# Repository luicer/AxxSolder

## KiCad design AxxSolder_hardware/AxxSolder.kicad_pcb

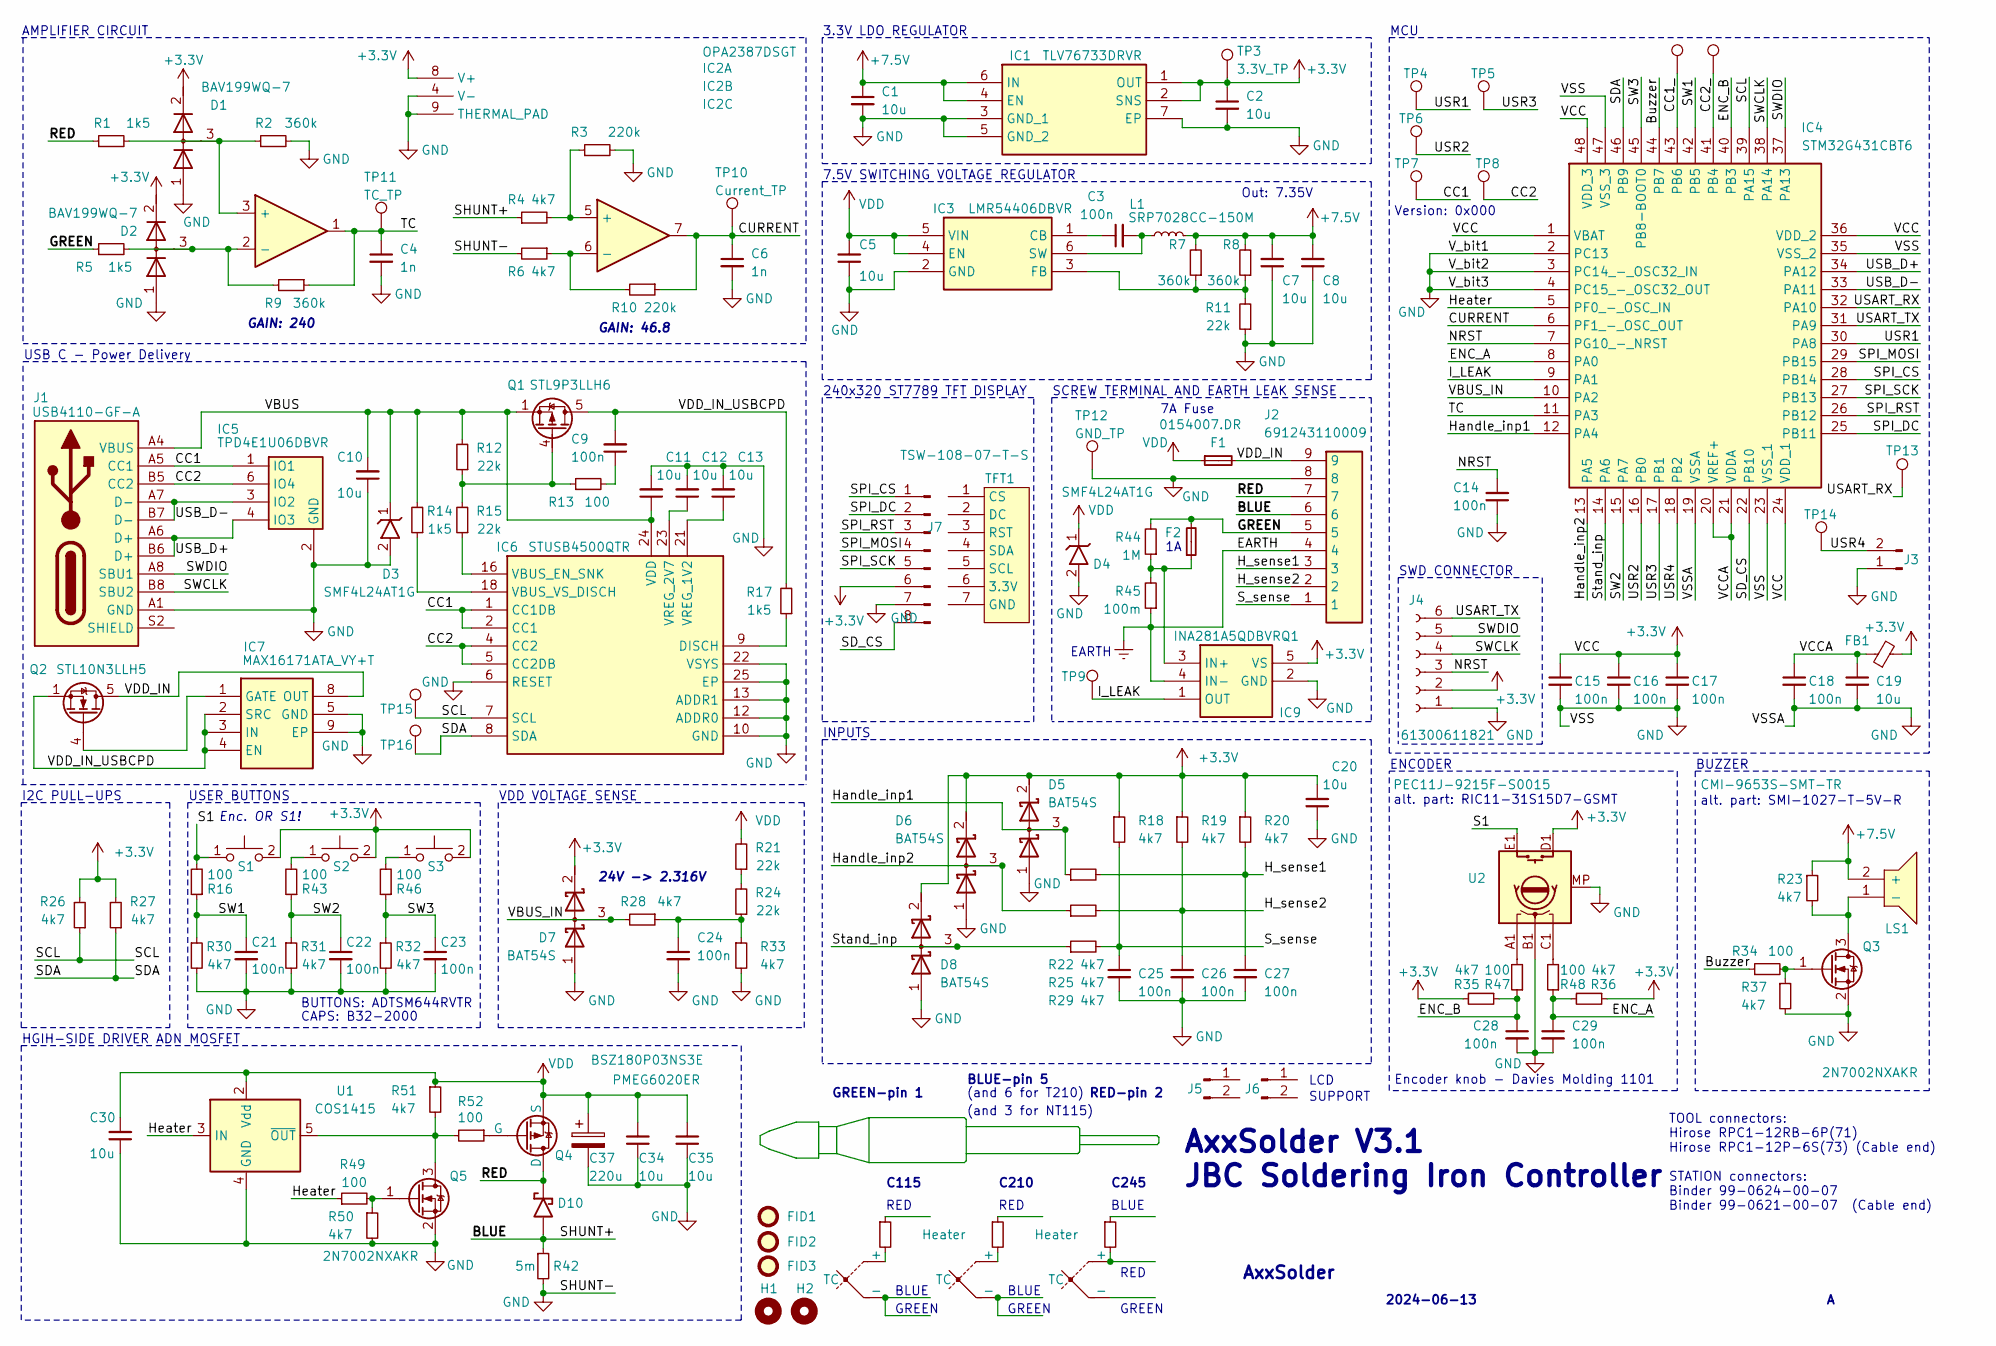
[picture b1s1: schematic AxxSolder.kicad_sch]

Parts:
C1, C2, C5, C7, C8, C10, C11, C12, C13, C19, C20, C30, C34, C35: 10u; C_0603_1608Metric; Manufacturer_Part_Number GRM188R6YA106MA73J; Mouser Part Number 81-GRM188R6YA106MA3J
C3, C9, C14, C15, C16, C17, C18, C21, C22, C23, C24, C25, C26, C27, C28, C29: 100n; C_0603_1608Metric; Manufacturer_Part_Number C0603C104J5RACTU; Mouser Part Number 80-C0603C104J5R
C4, C6: 1n; C_0603_1608Metric; Manufacturer_Part_Number C0603C102K3GAC; Mouser Part Number 80-C0603C102K3G
C37: 220u; CAPAE830X1050N; Mouser Part Number 80-EEV227M035A9MAA
D1, D2: BAV199WQ-7; SOT65P210X110-3N; Mouser Part Number 621-BAV199WQ-7
D3, D4: SMF4L24AT1G; SODFL3619X98N; Mouser Part Number 576-SMF4L24AT1G
D5, D6, D7, D8: BAT54S; SOT95P230X110-3N; Manufacturer_Part_Number BAT54S,215; Mouser Part Number 771-BAT54S-T/R
D10: PMEG6020ER; PMEG6020ER115; Mouser Part Number 771-PMEG6020ER-115
F1: 0154007.DR; 0154100DR; Mouser Part Number 576-0154007.DR
F2: SF-2410FP100W-2; SF2410FP100W2; Mouser Part Number 652-SF-2410FP100W-2
FB1: BLM18HE601SN1D; R_0603_1608Metric; Mouser Part Number 81-BLM18HE601SN1D
FID1, FID2, FID3: Fiducial; Fiducial_0.75mm_Mask1.5mm
H1, H2: MountingHole; MountingHole_2.5mm
IC1: TLV76733DRVR; SON65P200X200X80-7N; Mouser Part Number 595-TLV76733DRVR
IC2: OPA2387DSGT; VSSOP-8_3x3mm_P0.65mm; Mouser Part Number 595-OPA2387DSGT
IC3: LMR54406DBVR; SOT95P280X145-6N; Mouser Part Number 595-LMR54406DBVR
IC4: STM32G431CBT6; QFP50P900X900X160-48N; Mouser Part Number 511-STM32G431CBT6
IC5: TPD4E1U06DBVR; SOT95P280X145-6N; Mouser Part Number 595-TPD4E1U06DBVR
IC6: STUSB4500QTR; QFN50P400X400X100-25N-D; Mouser Part Number 511-STUSB4500QTR
IC7: MAX16171ATA_VY+T; SON50P300X200X80-9N; Mouser Part Number 700-MAX16171ATA/VY+T
IC9: INA281A5QDBVRQ1; SOT95P280X145-5N; Mouser Part Number 595-INA281A5QDBVRQ1
J1: USB4110-GF-A; USB4110GFA; Mouser Part Number 640-USB4110-GF-A
J2: 691243110009; Mouser Part Number 710-691243110009
J3: TSW-102-07-T-S; PinHeader_1x02_P2.54mm_Vertical; Mouser Part Number 200-TSW10207TS
J4: 61300611821; RHDR6W97P0X254_1X6_1574X250X865P; Mouser Part Number 710-61300611821
J5, J6: TSW-102-07-T-S; TSW-102-XX-YY-S; Mouser Part Number 200-TSW10207TS
J7: TSW-108-07-T-S; TSW-108-XX-YY-S; Mouser Part Number 200-TSW10807TS
L1: SRP7028CC-150M; INDPM7366X300N; Mouser Part Number 652-SRP7028CC-150M
LS1: CMI-9653S-SMT-TR; CMI9653SSMTTR; Mouser Part Number 490-CMI-9653S-SMT-TR
Q1: STL9P3LLH6; Mouser Part Number 511-STL9P3LLH6
Q2: STL10N3LLH5; Mouser Part Number 511-STL10N3LLH5
Q3, Q5: 2N7002NXAKR; SOT95P230X110-3N; Manufacturer_Part_Number 2N7002NXAKR; Mouser Part Number 771-2N7002NXAKR
Q4: BSZ180P03NS3E; TDSON-8-1
R1, R5, R14, R17: 1k5; R_0603_1608Metric; Manufacturer_Part_Number ERJ-H3ED1501V; Mouser Part Number 667-ERJ-H3ED1501V
R2, R7, R8, R9: 360k; R_0603_1608Metric; Manufacturer_Part_Number ERJ-3RED3603V; Mouser Part Number 667-ERJ-3RED3603V
R3, R10: 220k; R_0603_1608Metric; Manufacturer_Part_Number ERJ-3RED2203V; Mouser Part Number 667-ERJ-3RED2203V
R4, R6, R18, R19, R20, R22, R23, R25, R26, R27, R28, R29, R30, R31, R32, R33, R35, R36, R37, R50: 4k7; R_0603_1608Metric; Manufacturer_Part_Number ERJ-3RBD4701V; Mouser Part Number 667-ERJ-3RBD4701V
R11, R12, R15, R21, R24: 22k; R_0603_1608Metric; Manufacturer_Part_Number ERJ-UP3J223V; Mouser Part Number 667-ERJ-UP3J223V
R13, R16, R34, R43, R46, R47, R48, R49: 100; R_0603_1608Metric; Manufacturer_Part_Number ERJ-P03F1000V; Mouser Part Number 667-ERJ-P03F1000V
R39, R40: Heater
R41: Heater 2 OHM
R42: 5m; RESC6432X89N; Mouser Part Number 71-WSLP25125L000FEA
R44: 1M; R_0805_2012Metric; Manufacturer_Part_Number ERJ-6GEYJ105V; Mouser Part Number 667-ERJ-6GEYJ105V
R45: 100m; R_0805_2012Metric; Manufacturer_Part_Number ERJ-6DSFR10V; Mouser Part Number 667-ERJ-6DSFR10V
R51: 4k7; R_1210_3225Metric_Pad1.30x2.65mm_HandSolder; Manufacturer_Part_Number ERJ-3RBD4701V; Mouser Part Number 667-ERJ-3RBD4701V
R52: 100; R_0603_1608Metric; Manufacturer_Part_Number ERJ-3RBD4701V; Mouser Part Number 667-ERJ-3RBD4701V
S1, S2, S3: ADTSM644RVTR; Mouser Part Number 642-ADTSM644RVTR
TC1, TC2, TC3: TC
TFT1: Adafruit_240x320_TFT; Manufacturer_Part_Number 4311; Mouser Part Number 485-4311
TP1, TP2, TP4, TP5, TP6, TP7, TP8, TP14, TP15, TP16: DIAG_TP; TestPoint_Pad_D1.0mm
TP3: 3.3V_TP; TestPoint_Pad_D1.0mm
TP9, TP10: Current_TP; TestPoint_Pad_D1.0mm
TP11: TC_TP; TestPoint_Pad_D1.0mm
TP12: GND_TP; TestPoint_Pad_D1.0mm
TP13: DIAG_TP; TSW-101-XX-YY-S
U1: COS1415; SOT-23-5
U2: PEC11J-9215F-S0015; PEC11J9215FS0015; Mouser Part Number 652-PEC11J9215FS0015

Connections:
+3.3V: C2.1, C15.1, C16.1, C17.1, C20.2, D1.2, D2.2, D5.2 (K), D6.2 (K), D7.2 (K), D8.2 (K), FB1.2, IC1.1 (OUT), IC1.2 (SNS), IC2.8 (V+), IC4.1 (VBAT), IC4.24 (VDD_1), IC4.36 (VDD_2), IC4.48 (VDD_3), IC9.5 (VS), J4.2, J7.6, R18.1, R19.1, R20.1, R26.2, R27.2, R35.2, R36.1, S1.2, S2.2, S3.2, TP3.1, U2.D1
+7.5V: C1.1, C7.2, C8.2, IC1.4 (EN), IC1.6 (IN), L1.2, LS1.2 (+), R7.2, R8.2, R23.1
/BLUE: D10.2, J2.6, R4.1, R42.1
/Buzzer: IC4.44 (PB7), R34.1
/CC1: IC5.1 (IO1), IC6.1 (CC1DB), IC6.2 (CC1), J1.A5 (CC1), TP7.1
/CC1_: IC4.43 (PB6), TP1.1
/CC2: IC5.6 (IO4), IC6.4 (CC2), IC6.5 (CC2DB), J1.B5 (CC2), TP8.1
/CC2_: IC4.41 (PB4), TP2.1
/CURRENT: C6.1, IC2.7, IC4.6 (PF1_-_OSC_OUT), R10.1, TP10.1
/ENC_A: C29.1, IC4.8 (PA0), R36.2, R48.1
/ENC_B: C28.1, IC4.40 (PB3), R35.1, R47.1
/GREEN: F2.2, J2.5, R5.1, R44.2
/H_sense1: C27.1, J2.3, R20.2, R22.2
/H_sense2: C26.1, J2.2, R19.2, R25.2
/Handle_inp1: D5.3 (common), IC4.12 (PA4), R22.1
/Handle_inp2: D6.3 (common), IC4.13 (PA5), R25.1
/Heater: IC4.5 (PF0_-_OSC_IN), R49.1, U1.3 (IN)
/I_LEAK: IC4.9 (PA1), IC9.1 (OUT), TP9.1
/NRST: C14.2, IC4.7 (PG10_-_NRST), J4.3
/RED: D10.1, J2.7, Q4.5 (D), R1.1
/S1: R16.2, S1.1, U2.E1
/SCL: IC4.39 (PA15), IC6.7 (SCL), R26.1, TP15.1
/SDA: IC4.46 (PB9), IC6.8 (SDA), R27.1, TP16.1
/SD_CS: IC4.22 (PB10), J7.8
/SPI_CS: IC4.28 (PB14), J7.1
/SPI_DC: IC4.25 (PB11), J7.2
/SPI_MOSI: IC4.29 (PB15), J7.4
/SPI_RST: IC4.26 (PB12), J7.3
/SPI_SCK: IC4.27 (PB13), J7.5
/SW1: C21.1, IC4.42 (PB5), R16.1, R30.1
/SW2: C22.1, IC4.15 (PA7), R31.1, R43.1
/SW3: C23.1, IC4.45 (PB8-BOOT0), R32.1, R46.1
/SWCLK: IC4.38 (PA14), J1.B8 (SBU2), J4.4
/SWDIO: IC4.37 (PA13), J1.A8 (SBU1), J4.5
/S_sense: C25.1, J2.1, R18.2, R29.2
/Stand_inp: D8.3 (common), IC4.14 (PA6), R29.1
/TC: C4.1, IC2.1, IC4.11 (PA3), R9.1, TP11.1
/USART_RX: IC4.32 (PA10), TP13.1
/USART_TX: IC4.31 (PA9), J4.6
/USB_D+: IC4.34 (PA12), IC5.4 (IO3), J1.A6 (D+), J1.B6 (D+)
/USB_D-: IC4.33 (PA11), IC5.3 (IO2), J1.A7 (D-), J1.B7 (D-)
/USR1: IC4.30 (PA8), TP4.1
/USR2: IC4.16 (PB0), TP6.1
/USR3: IC4.17 (PB1), TP5.1
/USR4: IC4.18 (PB2), J3.2, TP14.1
/VBUS: C10.2, C11.1, D3.1 (K), IC6.24 (VDD), J1.A4 (VBUS), J1.A9 (VBUS), J1.B4 (VBUS), J1.B9 (VBUS), Q1.1 (S), R12.2, R14.2
/VBUS_IN: D7.3 (common), IC4.10 (PA2), R28.2
/VCCA: C18.1, C19.1, FB1.1, IC4.20 (VREF+), IC4.21 (VDDA)
/VDD_IN: F1.2, IC7.8 (OUT), J2.9, Q2.5 (D)
/VDD_IN_USBCPD: C9.2, IC7.2 (SRC), IC7.3 (IN), IC7.4 (EN), Q1.5 (D), Q2.1 (S), R17.2
Earth: IC9.4 (IN-), J2.4, R45.1
GND: C1.2, C2.2, C4.2, C5.1, C6.2, C7.1, C8.1, C10.1, C11.2, C12.2, C13.2, C14.1, C15.2, C16.2, C17.2, C18.2, C19.2, C20.1, C21.2, C22.2, C23.2, C24.2, C25.2, C26.2, C27.2, C28.2, C29.2, C30.1, C34.1, C35.1, C37.2, D1.1, D2.1, D3.2 (A), D4.2 (A), D5.1 (A), D6.1 (A), D7.1 (A), D8.1 (A), IC1.3 (GND_1), IC1.5 (GND_2), IC1.7 (EP), IC2.4 (V-), IC2.9 (THERMAL_PAD), IC3.2 (GND), IC4.2 (PC13), IC4.3 (PC14_-_OSC32_IN), IC4.4 (PC15_-_OSC32_OUT), IC4.19 (VSSA), IC4.23 (VSS_1), IC4.35 (VSS_2), IC4.47 (VSS_3), IC5.2 (GND), IC6.6 (RESET), IC6.10 (GND), IC6.12 (ADDR0), IC6.13 (ADDR1), IC6.22 (VSYS), IC6.25 (EP), IC7.5 (GND), IC7.9 (EP), IC9.2 (GND), J1.A1 (GND), J1.A12 (GND), J1.B1 (GND), J1.B12 (GND), J2.8, J3.1, J4.1, J7.7, Q3.2 (S), Q5.2 (S), R2.2, R3.2, R6.2, R11.1, R30.2, R31.2, R32.2, R33.2, R37.2, R42.2, R50.2, TP12.1, U1.4 (GND), U2.B1, U2.MP
unnamed: C9.1, R13.2
unnamed: C24.1, R24.1, R28.1, R33.1
unnamed: D1.3, IC2.3 (+), R1.2, R2.1
unnamed: D2.3, IC2.2 (-), R5.2, R9.2
unnamed: IC2.5 (+), R3.1, R4.2
unnamed: IC2.6 (-), R6.1, R10.2
unnamed: C3.1, IC3.1 (CB)
unnamed: IC3.3 (FB), R7.1, R8.1, R11.2
unnamed: C3.2, IC3.6 (SW), L1.1
unnamed: IC6.9 (DISCH), R17.1
unnamed: IC6.16 (VBUS_EN_SNK), R15.1
unnamed: IC6.18 (VBUS_VS_DISCH), R14.1
unnamed: C13.1, IC6.21 (VREG_1V2)
unnamed: C12.1, IC6.23 (VREG_2V7)
unnamed: IC7.1 (GATE), Q2.4 (G)
unnamed: F2.1, IC9.3 (IN+), R44.1, R45.2
unnamed: LS1.1 (-), Q3.3 (D), R23.2
unnamed: Q1.4 (G), R12.1, R13.1, R15.2
unnamed: Q3.1 (G), R34.2, R37.1
unnamed: Q4.4 (G), R52.1
unnamed: Q5.3 (D), R51.2, R52.2, U1.5 (~OUT)
unnamed: Q5.1 (G), R49.2, R50.1
unnamed: R21.1, R24.2
unnamed: R39.2, TC1.1 (+)
unnamed: R40.2, TC2.1 (+)
unnamed: R41.2, TC3.1 (+)
unnamed: R43.2, S2.1
unnamed: R46.2, S3.1
unnamed: R47.2, U2.A1
unnamed: R48.2, U2.C1
VDD: C5.2, C30.2, C34.2, C35.2, C37.1, D4.1 (K), F1.1, IC3.4 (EN), IC3.5 (VIN), Q4.1 (S), R21.2, R51.1, U1.2 (Vdd)

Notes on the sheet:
Version: 0x000
USER BUTTONS
C115
7A Fuse
Encoder knob - Davies Molding 1101
USB C - Power Delivery
BUTTONS: ADTSM644RVTR
Enc. OR S1!
MCU
CAPS: B32-2000
GREEN
(and 3 for NT115)
GREEN-pin 1
RED
LCD
alt. part: SMI-1027-T-5V-R
(and 6 for T210)
SCREW TERMINAL AND EARTH LEAK SENSE
AMPLIFIER CIRCUIT
24V -> 2.316V
VDD VOLTAGE SENSE
C245
ENCODER
SWD CONNECTOR
BLUE
BLUE-pin 5
2024-06-13
BUZZER
7.5V SWITCHING VOLTAGE REGULATOR
AxxSolder V3.1 JBC Soldering Iron Controller
TOOL connectors: Hirose RPC1-12RB-6P(71) Hirose RPC1-12P-6S(73) (Cable end) STATION connectors: Binder 99-0624-00-07 Binder 99-0621-00-07 (Cable end)
C210
INPUTS
EARTH
HGIH-SIDE DRIVER ADN MOSFET
AxxSolder
RED-pin 2
RED
Out: 7.35V
I2C PULL-UPS

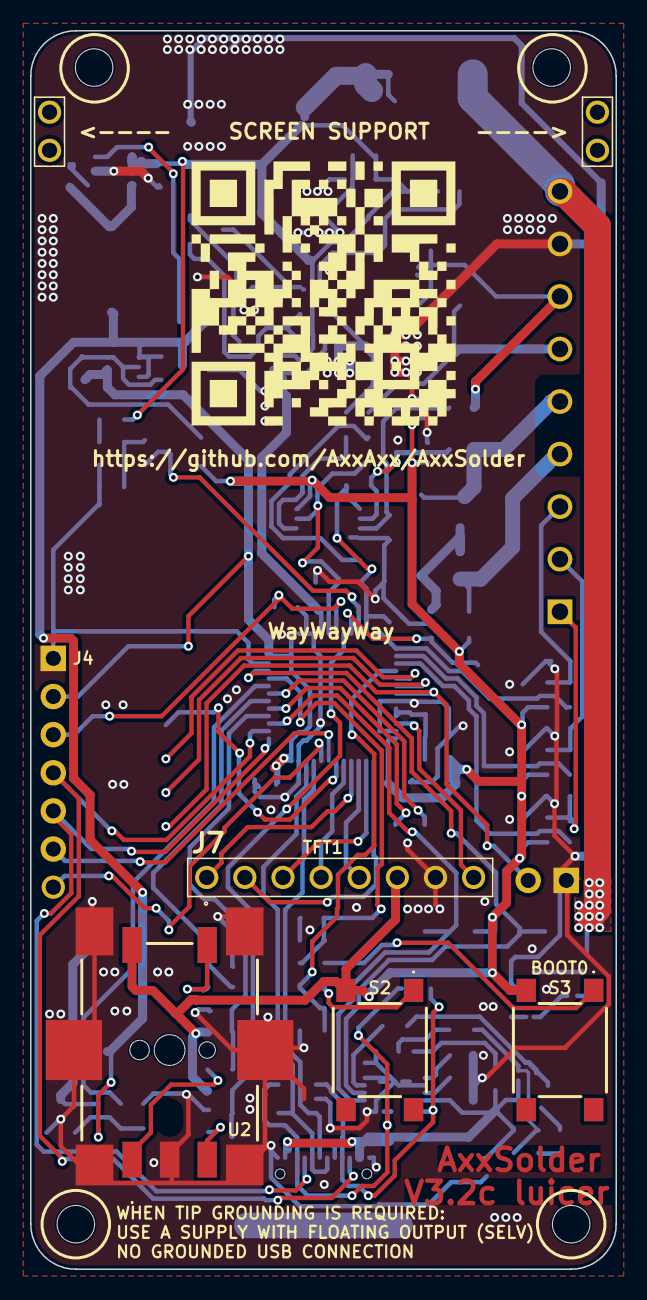
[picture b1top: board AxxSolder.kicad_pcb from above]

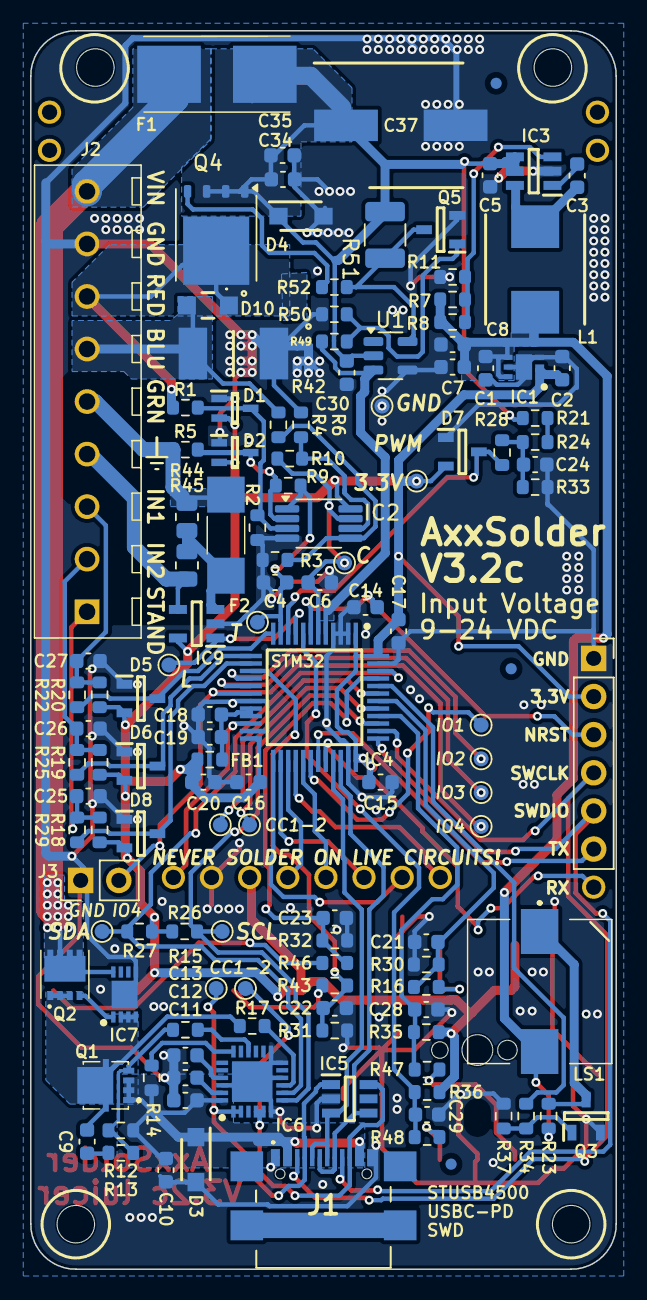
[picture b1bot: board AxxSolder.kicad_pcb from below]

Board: 2 copper layers, 39.0 x 82.5 mm, 141 parts (133 on the bottom side), 80 nets.

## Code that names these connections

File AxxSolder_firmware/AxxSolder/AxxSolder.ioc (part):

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Mcu.Name=STM32G431C(6-8-B)Tx
Mcu.Package=LQFP48
Mcu.UserName=STM32G431CBTx
PA0.GPIOParameters=GPIO_Label
PA0.GPIO_Label=ENC_A
PA0.Signal=S_TIM2_CH1
PA1.GPIOParameters=GPIO_Label
PA1.GPIO_Label=I_LEAK
PA1.Mode=IN2-Single-Ended
PA1.Signal=ADC2_IN2
PA10.Mode=Asynchronous
PA10.Signal=USART1_RX
PA13.Mode=Serial_Wire
PA13.Signal=SYS_JTMS-SWDIO
PA14.Mode=Serial_Wire
PA14.Signal=SYS_JTCK-SWCLK
PA15.Mode=I2C
PA15.Signal=I2C1_SCL
PA2.GPIOParameters=GPIO_Label
PA2.GPIO_Label=VBUS
PA2.Mode=IN3-Single-Ended
PA2.Signal=ADC1_IN3
PA3.GPIOParameters=GPIO_Label
PA3.GPIO_Label=THERMOCOUPLE
PA3.Mode=IN4-Single-Ended
PA3.Signal=ADC1_IN4
PA4.GPIOParameters=GPIO_Label
PA4.GPIO_Label=HANDLE_INP_1
PA4.Signal=GPIO_Input
PA5.GPIOParameters=GPIO_Label
PA5.GPIO_Label=HANDLE_INP_2
PA5.Signal=GPIO_Input
PA6.GPIOParameters=GPIO_Label
PA6.GPIO_Label=STAND_INP
PA6.Signal=GPIO_Input
PA7.GPIOParameters=GPIO_Label
PA7.GPIO_Label=SW_2
PA7.Signal=GPXTI7
PA8.GPIOParameters=GPIO_Label
PA8.GPIO_Label=USR_1
PA8.Signal=GPIO_Output
PA9.Mode=Asynchronous
PA9.Signal=USART1_TX
PB0.GPIOParameters=GPIO_Label
PB0.GPIO_Label=USR_2
PB0.Signal=GPIO_Output
PB1.GPIOParameters=GPIO_Label
PB1.GPIO_Label=USR_3
PB1.Signal=GPIO_Output
PB10.GPIOParameters=GPIO_Label
PB10.GPIO_Label=SPI2_SD_CS
PB10.Signal=GPIO_Output
PB11.GPIOParameters=GPIO_Label
PB11.GPIO_Label=SPI2_DC
PB11.Signal=GPIO_Output
PB12.GPIOParameters=GPIO_Label
PB12.GPIO_Label=SPI2_RST
PB12.Signal=GPIO_Output
PB13.Mode=Simplex_Bidirectional_Master
PB13.Signal=SPI2_SCK
PB14.GPIOParameters=GPIO_Label
PB14.GPIO_Label=SPI2_CS
PB14.Signal=GPIO_Output
PB15.Mode=Simplex_Bidirectional_Master
PB15.Signal=SPI2_MOSI
PB2.GPIOParameters=GPIO_Label
PB2.GPIO_Label=USR_4
PB2.Signal=GPIO_Output
PB3.GPIOParameters=GPIO_Label
PB3.GPIO_Label=ENC_B
PB3.Signal=S_TIM2_CH2
PB5.GPIOParameters=GPIO_Label
PB5.GPIO_Label=SW_1
PB5.Signal=GPXTI5
PB7.GPIOParameters=GPIO_Label
PB7.GPIO_Label=BUZZER
PB7.Signal=S_TIM4_CH2
PB8-BOOT0.GPIOParameters=GPIO_Label
PB8-BOOT0.GPIO_Label=SW_3
PB8-BOOT0.Signal=GPXTI8
PB9.Mode=I2C
PB9.Signal=I2C1_SDA
PC13.GPIOParameters=GPIO_Label
PC13.GPIO_Label=VERSION_BIT_1
PC13.Signal=GPIO_Input
PC14-OSC32_IN.GPIOParameters=GPIO_Label
PC14-OSC32_IN.GPIO_Label=VERSION_BIT_2
PC14-OSC32_IN.Signal=GPIO_Input
PC15-OSC32_OUT.GPIOParameters=GPIO_Label
PC15-OSC32_OUT.GPIO_Label=VERSION_BIT_3
PC15-OSC32_OUT.Signal=GPIO_Input
PF0-OSC_IN.GPIOParameters=GPIO_Label
PF0-OSC_IN.GPIO_Label=HEATER
PF0-OSC_IN.Mode=PWM Generation3 CH3N
PF0-OSC_IN.Signal=TIM1_CH3N
PF1-OSC_OUT.GPIOParameters=GPIO_Label
PF1-OSC_OUT.GPIO_Label=CURRENT
PF1-OSC_OUT.Mode=IN10-Single-Ended
PF1-OSC_OUT.Signal=ADC2_IN10
RCC.HSE_VALUE=8000000
RCC.SYSCLKFreq_VALUE=170000000
RCC.SYSCLKSource=RCC_SYSCLKSOURCE_PLLCLK
board=custom

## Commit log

2025-01-28 Actualización Esquema y PCB
